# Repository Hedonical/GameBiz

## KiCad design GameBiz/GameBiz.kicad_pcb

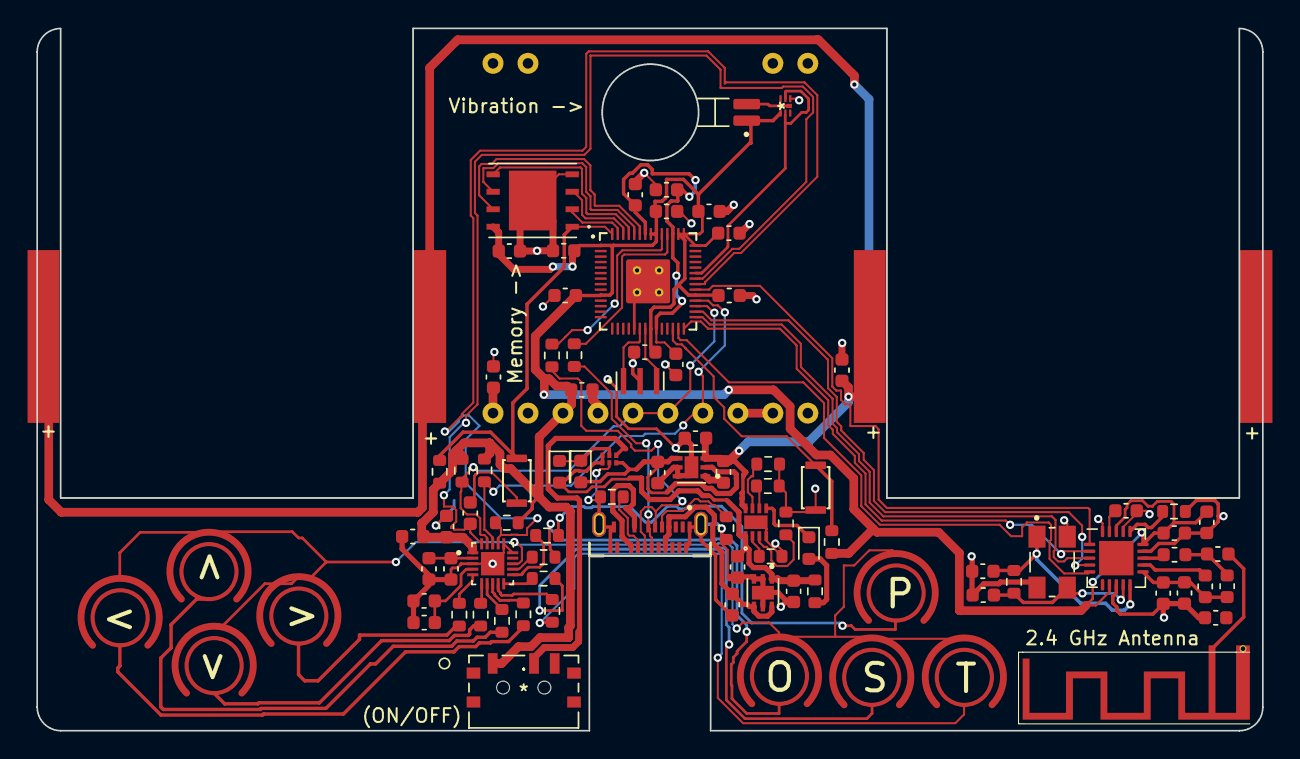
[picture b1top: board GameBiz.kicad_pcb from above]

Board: 2 copper layers, 89.0 x 51.0 mm, 94 parts (0 on the bottom side), 72 nets.

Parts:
2.4 GHz Antenna: Antenna_Loop; 2_4GHZANTENNA
(ON/OFF): .; CUS-12TB
<: SW; capacitivetouch
>: SW; capacitivetouch
>#2, >#3: SW; capacitivetouch
BT1, BT2: 1.2V; 24_5mmCoinCell
C1, C2, C3, C4, C5, C6, C7, C8, C9, C10, C11: 0.1uF; C_0603_1608Metric
C12, C13, C26, C27: 1uF; C_0603_1608Metric
C14: 4.7uF; C_0603_1608Metric
C15, C29, C33: 10uF; C_0603_1608Metric
C16, C18, C21: 100pF; C_0603_1608Metric
C17, C20: 2.2uF; C_0603_1608Metric
C19: 100nF; C_0603_1608Metric
C22: 33nF; C_0603_1608Metric
C23: 22uF; C_0603_1608Metric
C24: 10nF; C_0603_1608Metric
C25: 1nF; C_0603_1608Metric
C28: 2.2nF; C_0603_1608Metric
C30: 4.7pF; C_0603_1608Metric
C31: 1.5pF; C_0603_1608Metric
C32: 1pF; C_0603_1608Metric
C34, C35: 22pF; C_0603_1608Metric
D1, D2: D; D_0603_1608Metric
D3: LED; LED_0603_1608Metric
J1: USB4155-03-C_REVA; GCT_USB4155-03-C_REVA
L1: 2.7nH; L_0603_1608Metric
L2: 3.9nH; L_0603_1608Metric
L3: 8.2nH; L_0603_1608Metric
L4: 3.3uH; L_0603_1608Metric
M1: C0720B001F; XDCR_C0720B001F
O: SW; capacitivetouch
P: SW; capacitivetouch
Q1: Vibration ->; PMCXB900UEZ
R1, R2, R3, R4: 5.1K; R_0603_1608Metric
R5, R6: 27; R_0603_1608Metric
R7: 3K; R_0603_1608Metric
R8, R11, R12: 4.7K; R_0603_1608Metric
R9: 22K; R_0603_1608Metric
R10: 90; R_0603_1608Metric
R13: 27K; R_0603_1608Metric
R14: 36K; R_0603_1608Metric
R15: 10K; R_0603_1608Metric
R16, R17, R18, R19, R20, R21, R22, R23: 470; R_0603_1608Metric
R24: 1M; R_0603_1608Metric
S: SW; capacitivetouch
S1: RST; KXT321LHS
S2: BOOT; KXT321LHS
T: SW; capacitivetouch
U1: Memory ->; W25Q128JVPIQ TR
U2: RP2040
U3: NCV8718BMT330TBG; SON65P200X200X80-7N
U4: BQ25172DSGR
U5: 74LVC1G3157FZ4-7; 74LVC1G3157FZ4
U6: NRF24L01; QFN-20-1EP_4x4mm_P0.5mm_EP2.5x2.5mm
U7: IQS7222A001QNR; QFN40P300X300X60-21N
U8: TPS61291DRVT; SON65P200X200X80-7N
U9: EADOGS104NA
Y1: 12MHz; OSC_CSTNE12M0G55A000R0
Y2: ECS-160-18-30B-JEM-TR; XTAL_ECS-160-18-30B-JEM-TR

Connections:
+3.3V: (ON/OFF).1, C1.1, C2.2, C3.2, C4.2, C5.2, C6.2, C7.2, C8.2, C14.1, C16.1, C24.1, C25.1, C26.1, M1.1 (V+), Q1.4, R2.2, R3.2, R8.1, R11.1, R12.2, U1.8 (VDD), U2.1 (IOVDD), U2.10 (IOVDD), U2.22 (IOVDD), U2.33 (IOVDD), U2.42 (IOVDD), U2.43 (ADC_AVDD), U2.44 (VREG_VIN), U2.48 (USB_VDD), U2.49 (IOVDD), U6.7 (VDD), U6.15 (VDD), U6.18 (VDD), U7.1 (VDD), U9.13 (VDD)
GND: 2.4 GHz Antenna.3, BT2.2 (-), C1.2, C2.1, C3.1, C4.1, C5.1, C6.1, C7.1, C8.1, C9.1, C10.2, C11.1, C12.1, C13.1, C14.2, C15.2, C16.2, C17.2, C18.2, C19.2, C20.2, C21.2, C22.1, C23.1, C24.2, C25.2, C26.2, C27.1, C28.1, C29.1, C30.1, C32.1, C33.2, C34.2, C35.2, J1.A1 (GND_A), J1.A12 (GND_A), J1.B1 (GND_B), J1.B12 (GND_B), J1.S1 (SHELL_GND), J1.S2 (SHELL_GND), Q1.1, R1.1, R4.2, R7.2, R9.1, R13.2, R14.2, R15.1, S1.1, S2.1, U1.4 (GND), U1.9 (EP), U2.19 (TESTEN), U2.57 (GND), U3.2 (NC), U3.3 (GND), U3.5 (N/C), U3.7 (GND), U4.4 (GND), U4.9 (GND), U5.2 (GND), U6.8 (VSS), U6.14 (VSS), U6.17 (VSS), U6.20 (VSS), U7.3 (VSSD/VSSA), U7.15 (GPIO3), U7.16 (GPIO4), U7.21 (FLOAT), U8.5 (VSEL), U8.6 (GND), U8.7 (EXP), U9.12 (IM1), U9.14 (VSS), U9.18 (CS), U9.19 (SA0), Y1.2, Y2.2 (GND), Y2.4 (GND)
unnamed: 2.4 GHz Antenna.1, 2.4 GHz Antenna.2, C31.2, C32.2
unnamed: BT1.1 (+), C29.2, C33.1, L4.2, U4.8 (OUT), U8.3 (VIN)
unnamed: BT1.2 (-), BT2.1 (+)
unnamed: C9.2, C10.1, C11.2, U2.23 (DVDD), U2.45 (VREG_VOUT), U2.50 (DVDD)
unnamed: C12.2, J1.A4 (VBUS_A), J1.A9 (VBUS_A), J1.B4 (VBUS_B), J1.B9 (VBUS_B), U3.4 (EN), U3.6 (IN)
unnamed: C13.2, C15.1, D1.2 (A), R10.1, U3.1 (OUT), U4.1 (IN), U5.1, U5.6
unnamed: C17.1, C18.1, U7.2 (VREGD)
unnamed: C19.1, U2.36 (GPIO24), U7.20 (GPIO6)
unnamed: C20.1, C21.1, U7.4 (VREGA)
unnamed: C22.2, U6.19 (DVDD)
unnamed: C23.2, D2.2 (A), U5.3, U8.2 (VOUT), U8.4 (EN/BYP)
unnamed: C27.2, U9.11 (VOUT)
unnamed: C28.2, C30.2, L1.2, L3.2, U6.11 (VDD_PA)
unnamed: C31.1, L2.2, L3.1
unnamed: C34.1, R24.1, U6.10 (XC1), Y2.1 (IN/OUT)
unnamed: C35.1, R24.2, U6.9 (XC2), Y2.3 (OUT/IN)
unnamed: D1.1 (K), D2.1 (K), U5.5 (VCC)
unnamed: D3.1 (K), U4.5 (STAT)
unnamed: D3.2 (A), R10.2
unnamed: J1.A5 (CC1), R1.2
unnamed: J1.A6 (DP1), J1.B6 (DP2), R6.2
unnamed: J1.A7 (DN1), J1.B7 (DN2), R5.1
unnamed: J1.B5 (CC2), R4.1
unnamed: L1.1, U6.12 (ANT1)
unnamed: L2.1, U6.13 (ANT2)
unnamed: L4.1, U8.1 (SW)
unnamed: M1.2 (V-), Q1.7, Q1.8
unnamed: Q1.2, Q1.5, U2.37 (GPIO25)
unnamed: R2.1, S1.2, U2.26 (RUN)
unnamed: R3.1, S2.2, U1.1 (~CS), U2.56 (~QSPI_CS)
unnamed: R5.2, U2.46 (USB_D-)
unnamed: R6.1, U2.47 (USB_D+)
unnamed: R7.1, U4.2 (ISET)
unnamed: R8.2, U2.35 (GPIO23), U7.17 (GPIO5)
unnamed: R9.2, U6.16 (IREF)
unnamed: R11.2, U2.32 (GPIO21), U7.18 (GPIO2), U9.17 (SCLK)
unnamed: R12.1, U2.31 (GPIO20), U7.19 (GPIO1), U9.15 (SOD), U9.16 (SID)
unnamed: R13.1, U4.6 (TMR)
unnamed: R14.1, U4.7 (VSET)
unnamed: R15.2, U4.3 (TS)
unnamed: R16.1, U7.5 (CRX0)
unnamed: >#3.Rx, R16.2
unnamed: R17.1, U7.6 (CRX1)
unnamed: >.Rx, R17.2
unnamed: R18.1, U7.7 (CRX2)
unnamed: >#2.Rx, R18.2
unnamed: R19.1, U7.8 (CRX3)
unnamed: <.Rx, R19.2
unnamed: R20.1, U7.9 (CRX4)
unnamed: R20.2, T.Rx
unnamed: R21.1, U7.10 (CRX5)
unnamed: R21.2, S.Rx
unnamed: R22.1, U7.11 (CRX6)
unnamed: P.Rx, R22.2
unnamed: R23.1, U7.12 (CRX7)
unnamed: O.Rx, R23.2
unnamed: <.Tx, >.Tx, >#2.Tx, >#3.Tx, O.Tx, P.Tx, S.Tx, T.Tx, U7.13 (CTX8)
unnamed: (ON/OFF).2, U5.4
unnamed: U1.2 (DO/IO1), U2.55 (QSPI_SD1)
unnamed: U1.3 (~WP/IO2), U2.54 (QSPI_SD2)
unnamed: U1.5 (DI/IO0), U2.53 (QSPI_SD0)
unnamed: U1.6 (SCK), U2.52 (QSPI_SCLK)
unnamed: U1.7 (~HOLD/IO3), U2.51 (QSPI_SD3)
unnamed: U2.20 (XIN), Y1.1
unnamed: U2.21 (XOUT), Y1.3
unnamed: U2.27 (GPIO16), U6.5 (MISO)
unnamed: U2.28 (GPIO17), U6.2 (CSN)
unnamed: U2.29 (GPIO18), U6.3 (SCK)
unnamed: U2.30 (GPIO19), U6.4 (MOSI)
unnamed: U2.34 (GPIO22), U6.1 (CE)

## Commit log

2022-11-15 initial footprints and schematic
2022-11-17 initial schematic is finished
2022-11-18 layout almost finished
2022-11-18 capacitive buttons need to be finished
2022-11-19 finished initial layout, still some errors
2022-11-19 fixed most errors

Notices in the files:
parts and their libraries:
Copyright 2021 Accelerated Designs. All rights reserved.
